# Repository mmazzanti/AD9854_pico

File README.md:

# PicoDDS
A Raspberry Pico PCB board that can interface with the AD9854 (and similar others) DDS chips or evaluation boards through parallel port.

# V1.0_beta (future release)
This new version addresses one of the problems in the previous board (see release 0.9), the limit on the LDO current. The new version includes a LT1086 3.3V capable of up to 1.5A. This LDO version however is slightly obsolete, I would suggest to move to a LT1963A for future. At the moment I'm very satisfied with the version 0.9 and even if the LDO is at its limits and getting quite hot the board performs well since production (~ 4 months ago) in our lab.

### Please use always the last firwmare code provided, this is independent on the board version and getting updated/fixed from time to time.

# V0.9
## Why ?
This project was inspired by the necessity of having a simple python/serial interface to easily control older DDS evaluation boards (e.g. the  Eval-AD9854 here described).

The [Eval-AD9854](https://www.analog.com/en/design-center/evaluation-hardware-and-software/evaluation-boards-kits/EVAL-AD9854.html "Eval-AD9854") is an "old" evaluation board for the [AD9854](https://www.analog.com/en/products/ad9854.html "AD9854") Analog Devices DDS IC. The board permits programming of the AD9854 through a serial or parallel interface. 

While the AD9854 is still alive and in production at the time of writing, the word "old" refers to the serial port interface used in the Eval-AD9854 boards. 

Even though the provided software is not compatible with current Microsoft windows version the hardest part of programming the evaluation board comes from finding a parallel printer cable, perhaps from some electronics "museum".

If you are wondering what the parallel printer port on the Eval-AD9854 looks like, here it is:

Lukily this is not the only interface for programming the evaluation board. A 40 pins IDE port is also available on the board:

This looks like a perfect match for any Raspberry Pi board! A custom cable from a Raspberry Pi 3/4 to the Eval-9854 board could be made (as I did for the first prototyping), but this will require a cable per each DDS and a lot of soldering. 
A better idea would be to design a PCB board that interfaces a Raspberry Pi with the DDS evaluation board.
## Why the Pico ? Can I use any Raspberry Pi ?

Sure, any microcontroller capable of handling 21 digital pins can do the job. I decided on  a Raspberry Pico just because of its price tag and small form factor.

## How about powering up the board? 

The evaluation board needs a 3.3V power source to operate. This can also be provided by the same Raspberry. **BEWARE The Eval-9854 can request up to 1A of current at 3.3V, not all Raspberry pi boards can source that amount of power**. When not using the sinc filtering function of the DDS the power consumption goes reduces to ~750mA, when prototyping I used a Raspberry pi 400 and it handled the power hungry DDS quite decently. I would however suggest to power this board externally. The PCB board in this repository takes care also of that. I added a 1A LDO with a screw terminal where one can connect power cables to the Eval-9854; not very elegant, I know,but practical. 

## How to load the "firmware" on the board ? 

Once you are in possession of a PicoDDS board you will have to load on the Raspberry Pico the python source file that you find in the /src folder. The programming of the Pico happens through its micro USB connection. **The USB connection on the board is only for powering the Pico and the Eval-9854; it cannot be used to transfer data to the board!!**

First load a UF2 micropython image on your board (guide [here](https://www.raspberrypi.com/documentation/microcontrollers/micropython.html "micropython")) then load the /src/main.py script on your board. You can do that using [Thonny](https://thonny.org/ "Thonny"), VS code or whatever IDE is now in vogue.

## How to program the AD9854 ? 

The AD9854 permits various modes of operation:
- Single tone mode : in this mode we output a single pre-programmed frequency
- FSK : In this mode it is possible to switch between two pre-programmed frequencies
- Ramped FSK : As the previous but with ramping the frequency up/down when switching
- Chirp : A.k.a. as pulsed FM mode, starting from an initial frequency it ramps up (linearly or not linearly) for the programmed time.
- BPSK : Select between two pre-programmed phase offsets

More precise description can be found on the AD9854 datasheet.

## Why do I need this ?

My tipycal day usage of the AD9854 is to drive some AOM in our laboratory (check out [here](http://hyqs.nl/ "Hyqs") why we want to do that).

An [AOM](https://www.rp-photonics.com/acousto_optic_modulators.html "AOM") (Acousto Optic Modulator) is nothing more than a cyrstal vibrating at a certain frequency capable of steering a laser beam and adding-subtracting its resonating frequency to the diffracting beam (read more here ).

The typical resonating frequencies of AOM are between 70-300MHz although the coverage of this bandwith is mostly wavelength dependent.

In my case I needed a signal at 150MHz and I appeared to have found some Eval-AD9854 boards in some "storage" around (what a lucky find :blush: )

## Clocking the AD9854

One of the parameters hard coded in the main.py file is the clocking speed. The AD9854 can be clocked at 300MHz max. It has an internal PLL clock multiplier in case only slower clocks are available. The board I've been using so far has a 60MHz oscillator on it, however for more phase-dependent applications I plan to use a 10MHz clock reference from an atomic clock in future. The maximum clock multiplier is 20 that would mean that using directly a 10MHz clock and a x20 multiplier will push my clocking speed to 200MHz. In this case one can use a second DDS to generate a higher frequency clock or a second PLL clock multiplier.

Set the following variables depending on your clocking speed :
- SYSCLK : Provided clock speed (frequency of whatever you connect to the clock input port). In my case SYSCLK = 60E6.
- CLKMULT : Clock multiplier value, this will define the maximum frequency that can be generated by the DDS. In my case CLKMULT = 4 --> I'm clocking the DDS at 4*60MHz = 240MHz frequency and the highest output frequency I can get is 120MHz.
- WR_D_A(0x20, 0x60) : This is defined inside the _Init_AD9854()_ function. If you want to enable sinc filtering, replace it to _WR_D_A (0x20, 0x60) **BEWARE : This raises the total power consumption to 1.1A (1A AD9854 + 100mA for the Pico), which is 100mA higher than the on-board LDO's capability**. It should be enabled only when the Pico is connected through its micro-usb connection. In this configuration the mossfet will set the micro-usb as power source for the Pico and avoid over-loading the LDO. I will provide soon a V2 of the board with an updated LDO that can output up to 1.5A.
## How to use the micropython script

Various functions are available from the source script. These don't cover all the capabilities of the AD9854 but only what I need in the lab. More functions might be added in the future if I need them. Feel free to fork this repository if you want to add more!

After connecting to the Pico the following functions are available from the serial terminal.

- SingleTone(freq,ampl) : Turns on the AD9854 at the input frequency. freq must be declared in hertz. This corresponds to the single tone mode of the DDS. The amplitude of the signal can be selected with the "ampl" parameter [0-4095].
- on(freq,ampl) : To be used after initializing the DDS (by calling _SingleTone()_). Sets the output frequency and amplitude in single tone operational mode.
- off() : Turns off the DDS output (sets it to the lowest amplitude).
- UFSK(freq1, freq2, ampl) : Sets the AD9854 in FSK mode, the lowest frequency between freq1 and freq2 will be outputted immediately. To switch between the two frequencies one can use the Switch() function.
- RUFSK(freq1, freq2, ampl, delta, N) : Switches between freq1 and freq2 going through a linear ramp between the two. This corresponds to the ramped-FSK mode of the DDS. N is the number of steps the counter will need before switching to the next frequency. The switching period is given by (N-1)*system_clock. "delta" is the frequency step incremented each time the counter reaches 0
- Switch() : Switches between freq1 and freq2.

## No, I don't want to order your board!

Then no problem, the board just simplifies the connection. If you don't want to order a board or just test if the DDS works for you or any other reasons you can just connect 20 of the 40 pins connection to your Raspberry Pico (or 3/4) and start using generating RF frequencies immediately!
<br/>
<br/>
**BEWARE :** powering the DDS is now up to you. Find a 3.3V 1A power source (better if 1.5A).
<br/>
<br/>
Connect the Pico and the Eval-9854 as following:

- GP16 -> MRESET
- GP15 -> OSK
- GP17 -> PMODE
- GP14 -> RDB
- GP18 -> WRB
- GP13 -> I/O UD
- GP2 -> FSK (this can be found on the pin W9 on the board)
- GP19 -> A0
- GP12 -> A1
- GP20 -> A2
- GP11 -> A3
- GP21 -> A4
- GP10 -> A5
- GP22 -> D0
- GP9 -> D1
- GP8 -> D2
- GP7 -> D3
- GP6 -> D4
- GP5 -> D5
- GP4 -> D6
- GP3 -> D7

Or replace the Pins number in the python source file. A Raspberry pico can be connected using dupont wires as following :

Notice the black wire going on the pin W9, this is used for the FSK bit.

## Performances

### Switching time :

Time required to switch off -> on the RF signal.
It takes ~6ms from the moment one calls the _on(freq,ampl)_ (T=0 in the picture) to the moment when the AD9854 gives an output. 

### Frequency sweep :

This is an example of a frequency sweep :

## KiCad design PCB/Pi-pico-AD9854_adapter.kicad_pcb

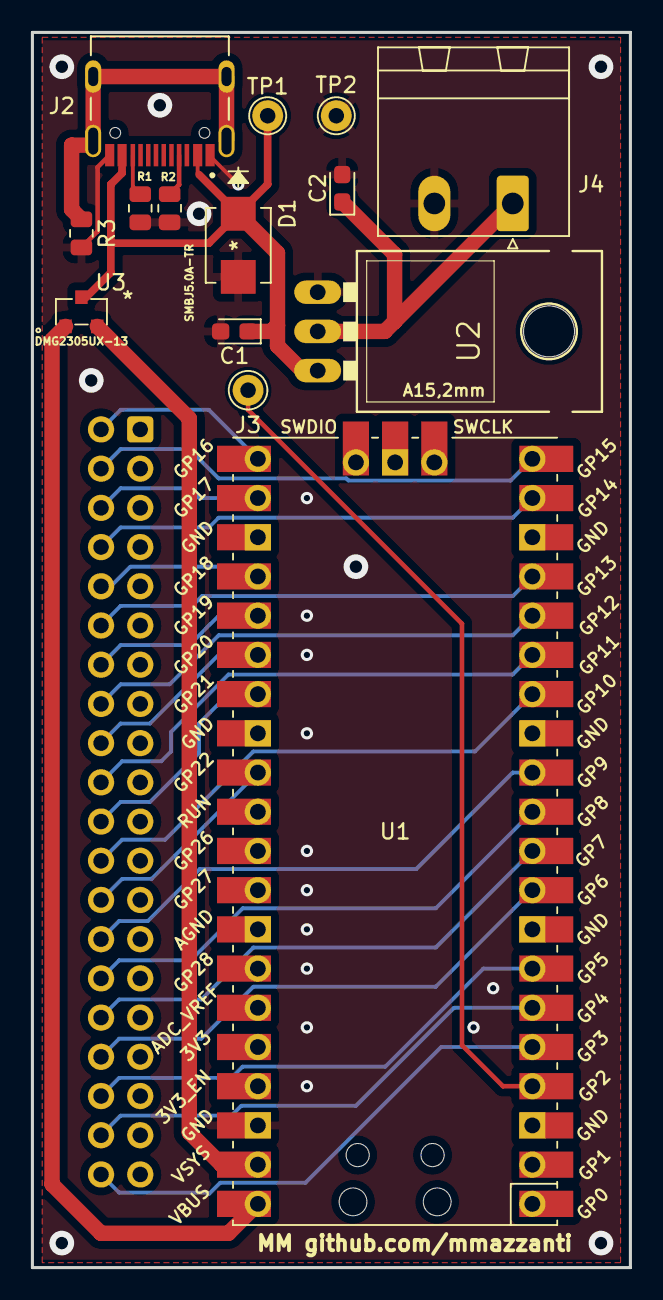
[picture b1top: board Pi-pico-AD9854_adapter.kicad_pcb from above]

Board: 2 copper layers, 38.7 x 80.0 mm, 15 parts (1 on the bottom side), 29 nets.

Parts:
C1, C2: 10uF; CP_EIA-2012-12_Kemet-R
D1: SMBJ5.0A-TR
J1: Conn_02x20_Odd_Even; IDC-Header_2x20_P2.54mm_Vertical
J2: TYPE-C-31-M-12; HRO_TYPE-C-31-M-12
J3: Conn_01x01_Male; Pin_D1.0mm_L10.0mm
J4: Screw_Terminal_01x02; PhoenixContact_MSTBA_2,5_2-G-5,08_1x02_P5.08mm_Horizontal
R1, R2: 5.1k; R_0805_2012Metric
R3: 0; R_0805_2012Metric
TP1, TP2: TestPoint; TestPoint_THTPad_D2.0mm_Drill1.0mm
U1: Pico; RPi_Pico_SMD_TH
U2: LT1086-3.3; LT1086
U3: DMG2305UX-13

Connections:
+3V3: C2.1, J4.1, U2.2 (VO)
+5V: C1.1, D1.1, J2.A4B9 (VBUS), TP1.1, U2.3 (VI), U3.3 (D)
A0: J1.14, U1.25 (GPIO19)
A1: J1.16, U1.16 (GPIO12)
A2: J1.18, U1.26 (GPIO20)
A3: J1.20, U1.15 (GPIO11)
A4: J1.22, U1.27 (GPIO21)
A5: J1.24, U1.14 (GPIO10)
D0: J1.26, U1.29 (GPIO22)
D1: J1.28, U1.12 (GPIO9)
D2: J1.30, U1.11 (GPIO8)
D3: J1.32, U1.10 (GPIO7)
D4: J1.34, U1.9 (GPIO6)
D5: J1.36, U1.7 (GPIO5)
D6: J1.38, U1.6 (GPIO4)
D7: J1.40, U1.5 (GPIO3)
FSK/BPSK: J3.1, U1.4 (GPIO2)
GND: C1.2, C2.2, D1.2, J2.A1B12 (GND), J4.2, R1.2, R2.2, R3.2, TP2.1, U1.38 (GND), U2.1 (GND)
I/O UD: J1.12, U1.17 (GPIO13)
MRESET: J1.2, U1.21 (GPIO16)
unnamed: J2.A5 (CC1), R2.1
unnamed: J2.B5 (CC2), R1.1
unnamed: J2.S1 (SHIELD), R3.1
unnamed: U1.39 (VSYS), U3.2 (S)
unnamed: U1.40 (VBUS), U3.1 (G)
OSK: J1.4, U1.20 (GPIO15)
PMODE: J1.6, U1.22 (GPIO17)
RDB: J1.8, U1.19 (GPIO14)
WRB: J1.10, U1.24 (GPIO18)

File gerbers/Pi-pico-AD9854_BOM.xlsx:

Comment | Designator | Footprint | JLCPCB Part #
0.47 uF | C1 | CAP-SMD_0805 | C13967
33uF | C2 | CAP-SMD_0805 | C432920
SMBJ5.0A-TR | D1 | SMB,DO-214AA | C130397
TYPE-C-31-M-12 | J2 | TYPE-C-31_L8.94_W7.3 | C165948
C81276 | J3 | SIP-1_2.54x2.54 | C81276
Screw_connector_terminal | J4 | SIP-2_7.8x10.0x5.0P | C8404
5.1K | R1 | RES-SMD_0805 | C17617
5.1K | R2 | RES-SMD_0805 | C17617
0 | R3 | RES-SMD_0805 | C728267
LT1086IM-3.3#TRPBF | U2 |  | C662441
DMG2305UX-7 | U3 | SOT-23-3 | C150470

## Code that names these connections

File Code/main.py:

from machine import Pin
import time


# Set here the input clock, I'm using a board with a 20MHz oscillator
# Set to 10MHz if connected to the atomic clock 
SYSCLK = 60E6;
# Set clock multiplier (that will determine the frequency precision)
# Max output freq is 1/2 F * (MULT * CLK)
# The AD9854 has an internal PLL 
CLKMULT = 4;

# Addresses for F1 & F2
addrF1 = 4;
addrF2 = 10;
addrDelta = 16;



# Define the GPIO pins
mreset = Pin(16, Pin.OUT) 
osk = Pin(15, Pin.OUT) 
pmode = Pin(17, Pin.OUT) 
rdb = Pin(14, Pin.OUT) 
wrb = Pin(18, Pin.OUT) 
ioud = Pin(13, Pin.OUT)
fsk = Pin(2, Pin.OUT)
a0 = Pin(19, Pin.OUT) 
a1 = Pin(12, Pin.OUT) 
a2 = Pin(20, Pin.OUT) 
a3 = Pin(11, Pin.OUT) 
a4 = Pin(21, Pin.OUT) 
a5 = Pin(10, Pin.OUT) 
d0 = Pin(22, Pin.OUT) 
d1 = Pin(9, Pin.OUT) 
d2 = Pin(8, Pin.OUT) 
d3 = Pin(7, Pin.OUT) 
d4 = Pin(6, Pin.OUT) 
d5 = Pin(5, Pin.OUT)
d6 = Pin(4, Pin.OUT)
d7 = Pin(3, Pin.OUT)

trigger = Pin(0, Pin.OUT)

led = Pin(25, Pin.OUT)


addresses = [a5, a4, a3, a2, a1, a0]
datas = [d7, d6, d5, d4, d3, d2, d1, d0]
masks = [int('10000000', 2), int('01000000', 2), int('00100000', 2), int('00010000', 2), int('00001000', 2), int('00000100', 2), int('00000010', 2), int('00000001', 2)]
masks2 = [int('00100000', 2), int('00010000', 2), int('00001000', 2), int('00000100', 2), int('00000010', 2), int('00000001', 2)]

def WR_D_A(addr, data):
    # Write data to address
    for i,a in enumerate(addresses) :
        a.on() if addr & masks[i+2] == masks[i+2] else a.off()
        #print("a",i,": on") if addr & masks[i] == masks[i] else print("a",i, ": off")

    # Write data to data
    for j,d in enumerate(datas) :
        d.on() if data & masks[j] == masks[j] else d.off()
        #print("d",i,": on") if data & masks[i] == masks[i] else print("d",i, ": off")
    wrb.off()
    wrb.on()
    
    #print(addr&int('11111111', 2), " : ",data&int('11111111', 2))

# Clocks the external update clock 
# this works if pin 20 is set to 0 when writing the registers
# otherwise the internal clock has to be used an synchronized to the raspberry
def Update_CLK():
    ioud.on()
    ioud.off()

def Init_AD9854(mode):
    # Set device in parallel mode
    pmode.on()
    # Set the WRB pin to high
    wrb.on()
    # Set the RDB pin to high
    rdb.on()
    # Set the I/O UD pin to low
    ioud.off()
    # Set the MRESET pin to high
    mreset.on()
    # Set the MRESET pin to low
    mreset.off()
    # No mode should be powered off
    # No power saving
    WR_D_A(0x1d, 0x00)
    WR_D_A(0x1e, CLKMULT)
    #Set sysmode to 0x00 (no internal update clock!)
    WR_D_A(0x1f, mode)
    #OSK EN, Keep sinc filter enabled
    #WR_D_A(0x20, 0x60)
    #OSK EN, disable sinc filter (300mA less current needed)
    WR_D_A(0x20, 0x20)
    Update_CLK()


# Resets accumulators :
# N = 2 Resets ACC 1 (10)
# N = 1 Resets ACC 2 (01)
# N = 3 Resets ACC 1 & 2 (11)
def Rst_ACC(N,mode):
    # Assuming this happens always after a init this is not needed
    #WR_D_A(0x1f, (0x00)+mode)
    WR_D_A(0x1f, (N<<6)+mode)
    WR_D_A(0x1f, mode)
    Update_CLK()

# Calculates the 2-complement of a int
def twos_comp(val, bits):
    if (val & (1 << (bits - 1))) != 0: # if sign bit is set e.g., 8bit: 128-255
        val = val - (1 << bits)        # compute negative value
    return val                         # return positive value as is


# Set_frequency sets frequency and amplitude
# Frequency (max CLK/2)
# Amplitude (max 4096)
def Set_freq(freq,ampl,N):
    # FTW for calculating the bit frequency
    FTW = round((freq*(2**48))/(SYSCLK*CLKMULT));
    # Set frequency addresses [4,9] to FTW
    for i in range(6):
        WR_D_A(N+i,FTW>>(40-8*i)) 
    # Set I channel ampl addresses 0x[21,22] to amlitude
    if ampl > 0 :
        WR_D_A(0x21, ampl>>8 )
        WR_D_A(0x22, ampl)
        # Set Q channel ampl addresses 0x[21,22] to amlitude
        WR_D_A(0x23, ampl>>8 )
        WR_D_A(0x24, ampl)
    #Update_CLK()
    
def Set_ramprate(N):
    WR_D_A(0x1a, N>>16)
    WR_D_A(0x1b, N>>8)
    WR_D_A(0x1c, N)
    

def SingleTone(freq):
    Init_AD9854(0x00)
    on(freq)

def on(freq):
    Set_freq(freq,1095,addrF1)
    Update_CLK()
    led.on()
    
def off():
    Set_freq(0,0,addrF1)
    led.off()
    trigger.off()
    
def UFSK(freq1,freq2):
    fsk.off()
    Init_AD9854(0x2)
    Set_freq(freq1,1095,addrF1)
    Set_freq(freq2,-1,addrF2)
    Update_CLK()
    led.on()
    
def RUFSK(freq1,freq2,delta,N):
    fsk.off()
    Init_AD9854(0x4)
    Rst_ACC(2,0x4)
    # Sets Ramped FSK with triangle ramp shape
    if freq1 < freq2:
        # Set initial freq
        Set_freq(freq1,1095,addrF1)
        # Set final freq
        Set_freq(freq2,-1,addrF2)
    else :
        # Set initial freq
        Set_freq(freq2,1095,addrF1)
        # Set final freq
        Set_freq(freq1,-1,addrF2)
    # Set frequency step
    Set_freq(twos_comp(delta, 48),-1,addrDelta)
    # Set period (N+1)*System CLK
    Set_ramprate(N)
    Update_CLK()
    led.on()
    
def Switch():
    fsk.toggle()

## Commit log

2022-04-10 PCB board V1
2022-04-10 Added documentation, turned sinc filter off by default
2022-04-10 Update README.md
    Fixed few typos
2022-04-10 Added gerbers and BOM
2022-04-10 + jokes - typos
2022-04-11 Bug fixing
2022-04-11 Added SingleTone(), modified on()
2022-04-11 Added pdf schematics
2022-04-11 removed backups
2022-04-11 remove backup files
2022-07-27 V1.0_beta prototype. Firwmare fixes

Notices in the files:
parts and their libraries:
Copyright 2021 Accelerated Designs. All rights reserved.
